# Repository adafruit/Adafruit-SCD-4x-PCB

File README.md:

## Adafruit SCD-4x CO2, Temperature and Humidity Sensor PCB

<br/>
<br/>
Click above to purchase one from the Adafruit shop!

PCB files for the Adafruit SCD-4x CO2, Temperature and Humidity Sensor. 

Format is EagleCAD schematic and board layout
* https://www.adafruit.com/product/5190

### Description

Take a deep breath in...now slowly breathe out. Mmm isn't it wonderful? All that air around us, which we bring into our lungs, extracts oxygen from and then breathes out carbon dioxide. CO2 is essential for life on this planet we call Earth - we and plants take turns using and emitting CO2 in an elegant symbiosis. But it's important to keep that CO2 balanced - you don't want too much around, not good for humans and not good for our planet.

The SCD-40 is a photoacoustic 'true' CO2 sensor that will tell you the CO2 PPM (parts-per-million) composition of ambient air. Unlike the SGP30, this sensor isn't approximating it from VOC gas concentration - it really is measuring the CO2 concentration! That means it's bigger and more expensive, but it is the real thing. Perfect for environmental sensing, scientific experiments, air quality and ventilation studies, and more.

Compared to the illustrious SCD-30, this sensor uses a different measurement technique, which allows it to be much smaller. The overall data quality should be very similar, however. Like the SCD-30, this sensor has data read over I2C, so it works very nicely with just about any microcontroller or microcomputer. There's both Arduino and Python/CircuitPython code so you can get started in a jiffy.

There are two variants of this sensor - the SCD-40 and SCD-41

* The SCD-40 is lower cost, and is perfect for indoor/outdoor air quality and CO2 measurements. It has a range of 400~2000 ppm with an accuracy of ±(50 ppm + 5% of reading)
* The SCD-41 is more expensive, and while it can definitely be used for air quality, it's wide range means its best used for industrial or scientific CO2 measurements where the ppm can get very high. It has a range of 400~5000 ppm with an accuracy of ±(40 ppm + 5% of reading)

Nice sensor, right? So we made it easy for you to get right into your next project. The sensor is soldered onto a custom-made PCB in the STEMMA QT form factor, making them easy to interface with. The STEMMA QT connectors on either side are compatible with the SparkFun Qwiic I2C connectors. This allows you to make solderless connections between your development board and the SCD-4x or to chain it with a wide range of other sensors and accessories using a compatible cable.

This sensor can run from 3.3 to 5V but it's more important for it to have a quiet power supply with low ripple, than any particular voltage. For that reason we've added a 3.3V regulator and level shifters: when connecting to a 5V microcontroller like an Arduino UNO the 5V supply is often shared with other electronic components that add noise. The onboard regulator will keep the voltage nice and quiet. For advanced hackers, they can cut/solder the back traces to change whether the regulator is enabled and what I2C logic level is desired.

### License

Adafruit invests time and resources providing this open source design, please support Adafruit and open-source hardware by purchasing products from [Adafruit](https://www.adafruit.com)!

Designed by Limor Fried/Ladyada for Adafruit Industries.

Creative Commons Attribution/Share-Alike, all text above must be included in any redistribution. 
See license.txt for additional details.

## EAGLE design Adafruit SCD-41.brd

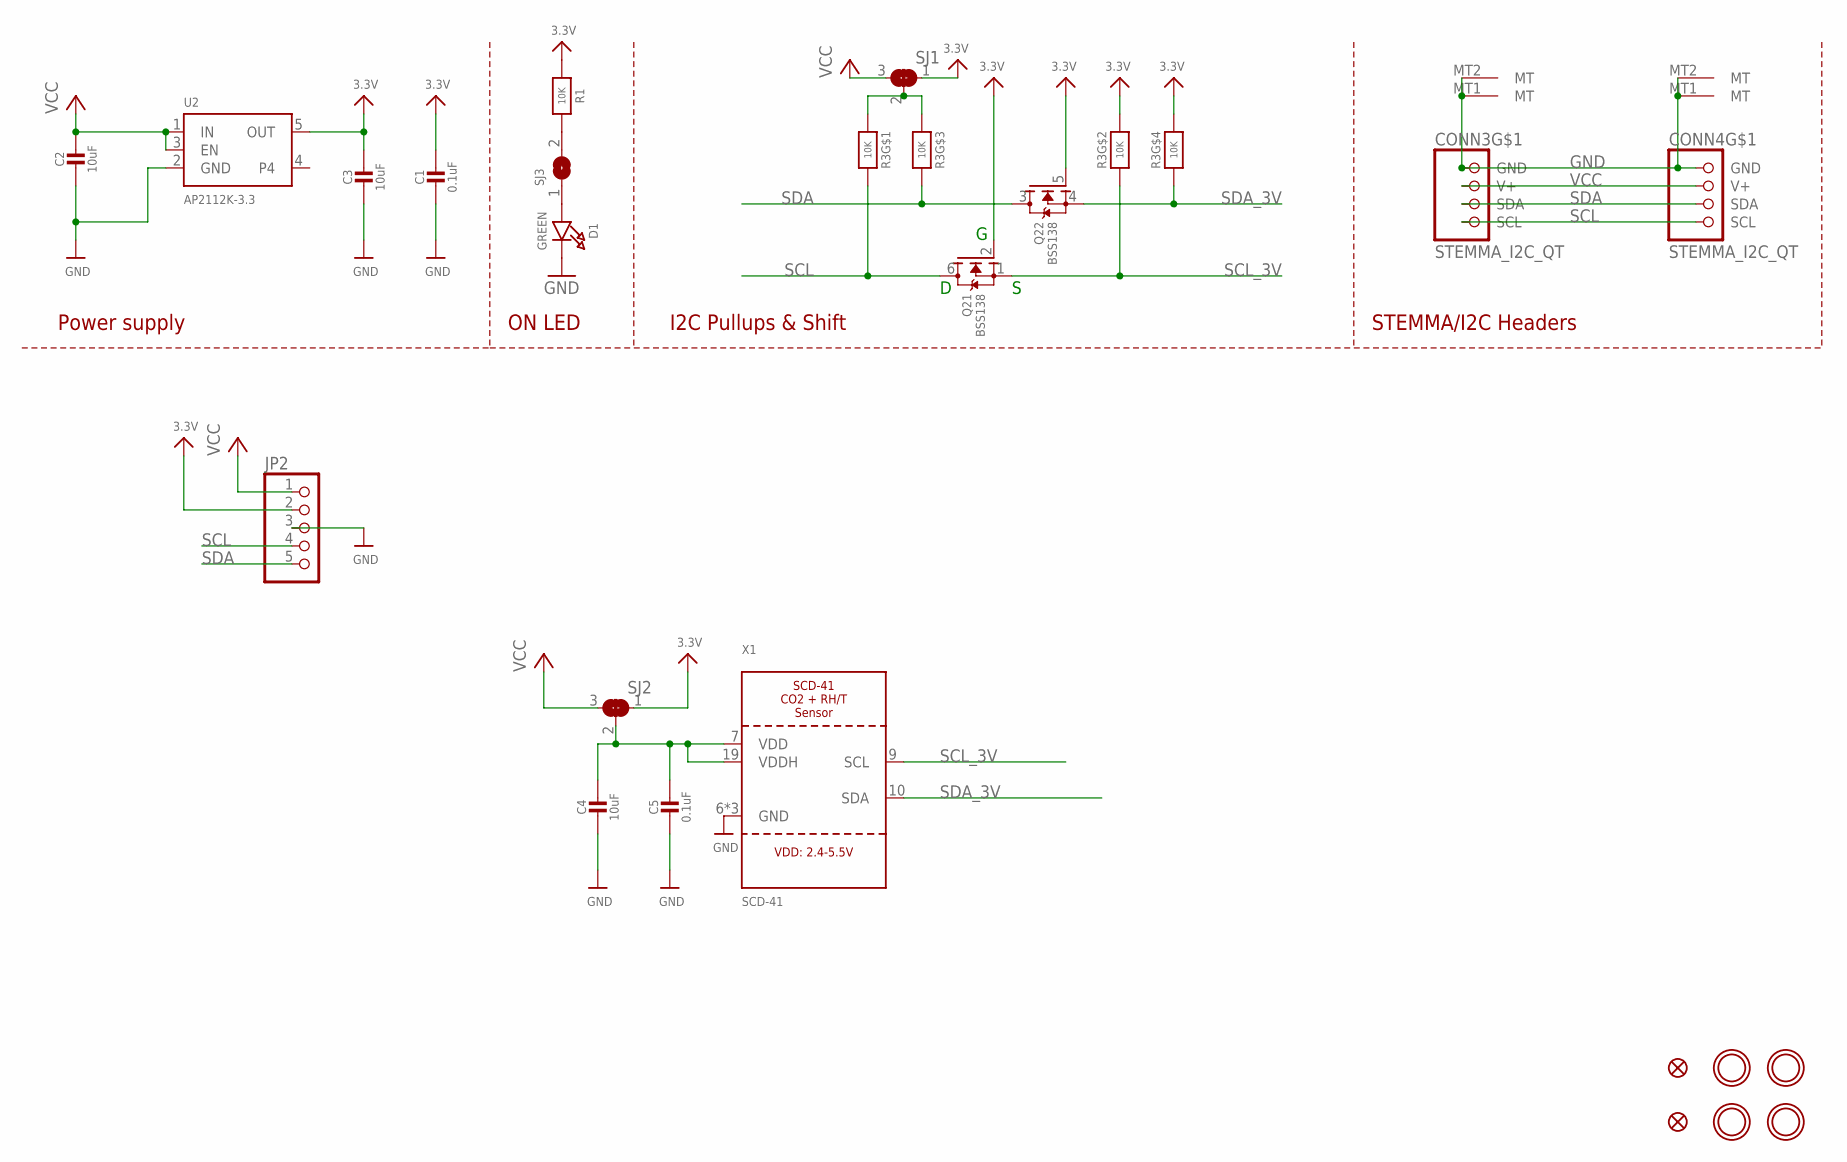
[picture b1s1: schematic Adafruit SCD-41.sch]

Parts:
C1, C5: 0.1uF; 0603-NO
C2, C3, C4: 10uF; 0805-NO
CONN3, CONN4: STEMMA_I2C_QT; JST_SH4
D1: GREEN; CHIPLED_0603_NOOUTLINE
FID3, FID4: FIDUCIAL_1MM
JP2: HEADER-1X576MIL; 1X05_ROUND_76
Q2: BSS138; SOT363
R1: 10K; 0603-NO
R3: 10K; RESPACK_4X0603
SJ1, SJ2: SOLDERJUMPER_2WAY; SOLDERJUMPER_2WAY_OPEN_NOPASTE
SJ3: SOLDERJUMPERCLOSED; SOLDERJUMPER_CLOSEDWIRE
U2: AP2112K-3.3; SOT23-5
U$1, U$17, U$19, U$21: MOUNTINGHOLE3.0THIN; MOUNTINGHOLE_3.0_PLATEDTHIN
X1: SCD-41; SCD41

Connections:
3.3V: C1.1, C3.1, JP2.2, Q2.2 (G), Q2.5 (G), R1.1, R3.2 (1), R3.4 (1), SJ1.1, SJ2.1, U2.5 (OUT)
GND: C1.2, C2.2, C3.2, C4.2, C5.2, CONN3.1 (GND), CONN3.MT1 (MT), CONN3.MT2 (MT), CONN4.1 (GND), CONN4.MT1 (MT), CONN4.MT2 (MT), D1.C, JP2.3, U2.2 (GND), X1.6 (GND), X1.20 (GND), X1.P$1 (GND)
unnamed: D1.A, SJ3.1
unnamed: R3.1, R3.3 (1), SJ1.2
unnamed: C4.1, C5.1, SJ2.2, X1.7 (VDD), X1.19 (VDDH)
unnamed: R1.2, SJ3.2
SCL: CONN3.4 (SCL), CONN4.4 (SCL), JP2.4, Q2.6 (D), R3.8 (2)
SCL_3V: Q2.1 (S), R3.7 (2), X1.9 (SCL)
SDA: CONN3.3 (SDA), CONN4.3 (SDA), JP2.5, Q2.3 (D), R3.6 (2)
SDA_3V: Q2.4 (S), R3.5 (2), X1.10 (SDA)
VCC: C2.1, CONN3.2 (V+), CONN4.2 (V+), JP2.1, SJ1.3, SJ2.3, U2.1 (IN), U2.3 (EN)

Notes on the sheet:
I2C Pullups & Shift
STEMMA/I2C Headers
ON LED
Power supply

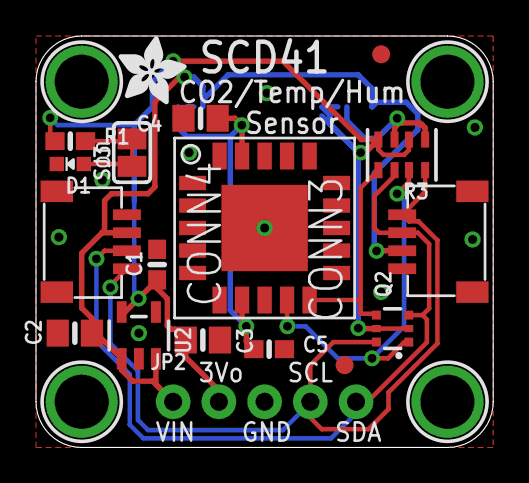
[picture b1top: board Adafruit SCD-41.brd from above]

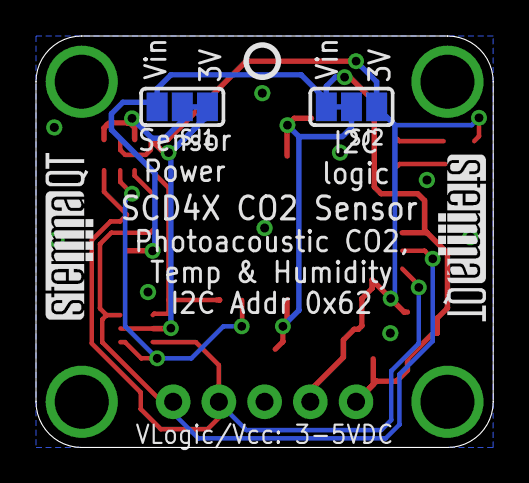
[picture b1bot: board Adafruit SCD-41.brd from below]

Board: 2 copper layers, 25.4 x 22.9 mm, 27 parts (5 on the bottom side), 11 nets.

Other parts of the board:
U$22: ADAFRUIT_3.5MM
U$25: PCBFEAT-REV-040
U$30, U$31: STEMMAQT

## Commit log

2021-08-25 Adding board files.

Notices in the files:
parts and their libraries:
microbuilder: This work is placed in the public domain, and may be freely used for commercial and non-commercial work with the following conditions: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
